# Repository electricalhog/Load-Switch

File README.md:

# Load-Switch
In here are the files used in making the load switch sold on tindie
- Load_Switch.brd is the Eagle board file
- Load_Switch.sch is the Eagle schematic file
- Load_Switch_v1.zip is the zip folder containing the gerber files
- main.c is the code created in atmel studio for the attiny10

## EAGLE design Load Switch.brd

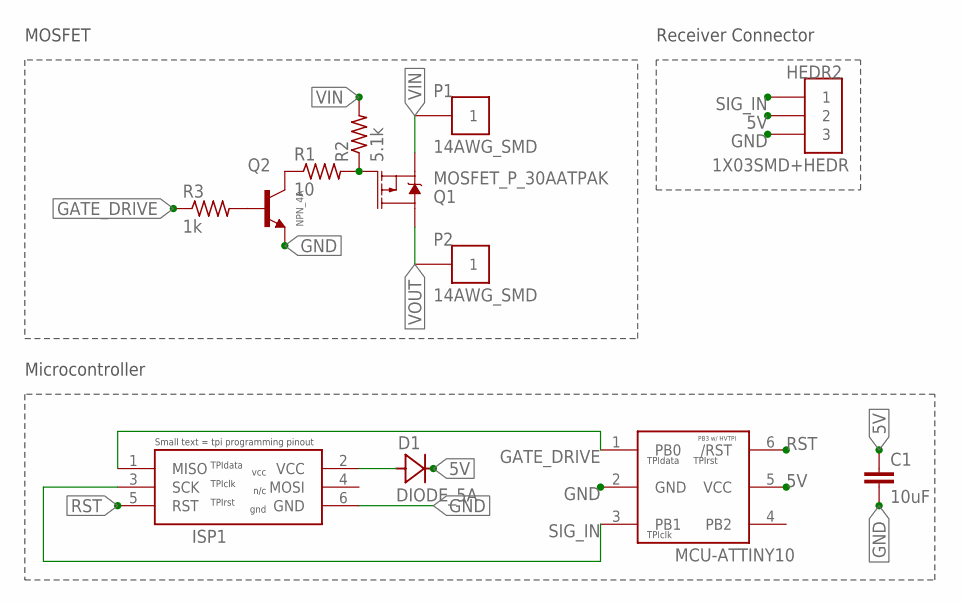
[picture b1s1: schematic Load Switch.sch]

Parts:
C1: 10uF; 1206
D1: DIODE_5A; DO-214AC
HEDR2: 1X03SMD+HEDR; 1X3_SMD+HEDR
IC1: MCU-ATTINY10; SOT23-6
ISP1: CON-ICSP/ISP-AVR-POGO; 2X3_POGO_AVR
P1, P2: 14AWG_SMD; 14AWG_PAD
Q1: MOSFET_P_30AATPAK; TO-252/DPAK
Q2: NPN_4A; SOT23-3
R1: 10; TG-0603
R2: 5.1k; TG-0603
R3: 1k; TG-0603

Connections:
5V: C1.1, D1.1 (C), HEDR2.2, IC1.5 (VCC)
GATE: Q2.3 (C), R1.1
GATE_DRIVE: IC1.1 (PB0), ISP1.1 (MISO), R3.1
GND: C1.2, HEDR2.3, IC1.2 (GND), ISP1.6 (GND), Q2.2 (E)
unnamed: Q1.1 (G), R1.2, R2.1
unnamed: Q2.1 (B), R3.2
unnamed: D1.2 (A), ISP1.2 (VCC)
RST: IC1.6 (/RST), ISP1.5 (RST)
SIG_IN: HEDR2.1, IC1.3 (PB1), ISP1.3 (SCK)
VIN: P1.PAD, Q1.3 (S), R2.2
VOUT: P2.PAD, Q1.2 (D)

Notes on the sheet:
Receiver Connector
MOSFET
Microcontroller

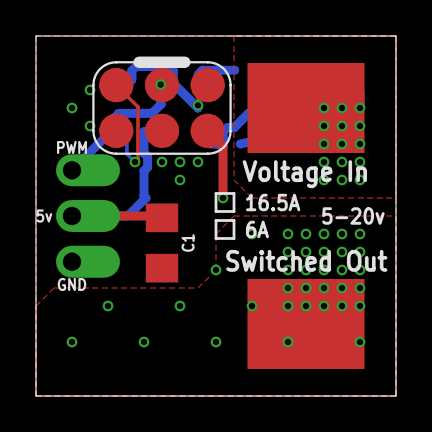
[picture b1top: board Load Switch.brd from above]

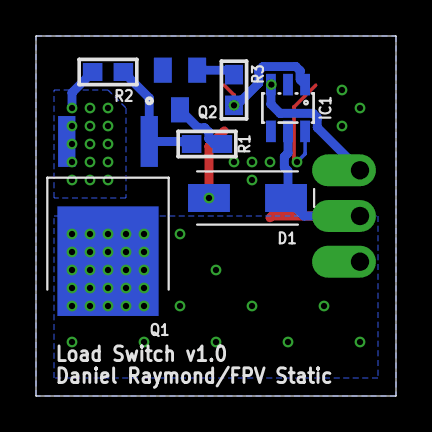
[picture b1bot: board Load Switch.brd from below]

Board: 2 copper layers, 20.0 x 20.0 mm, 12 parts (7 on the bottom side), 11 nets.

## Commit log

2020-01-12 Upload code and design files for the load switch

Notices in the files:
parts and their libraries:
SparkFun-Capacitors: Licensing: Creative Commons ShareAlike 4.0 International - https://creativecommons.org/licenses/by-sa/4.0
